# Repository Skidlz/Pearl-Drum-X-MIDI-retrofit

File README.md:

# Pearl Drum-X MIDI retrofit
 A MIDI retrofit board for Pearl's Drum-X (DRX-1) drum synthesizer

The project is designed around an Atmega*8 that controls a MAX528 octal DAC.

### Install Guide
[Here](https://docs.google.com/document/d/1SWIhVnxzadJWSYvPP88jSyq_Yxp76ufy1qYrGyIhOZM/edit?usp=sharing) is a quick explanation of the connections that need to be made to install the board.

### DAC
Five DAC outputs are used to generate triggers with different voltages based on MIDI velocity.

One output is used to generate eight control voltages for each of the five voices. Timing signals are received from the Pearl's motherboard, and are used to syncronize the stream of multiplexed CV signals.

### Use
The boards starts up in "MIDI learn" mode, and loads default settings for each voice. The board will assign itself to the first channel it receives a message on. The notes that it responds to, and the voice defaults are hard-coded in the firmware.

The voice paramaters are mapped to the first 40 MIDI CCs in this order: Pitch, Bend, Osc/Noise Mix, Over Tone, Attack, Filter, Decay, Level

### Atmega328p
The fuse bits of the Atmega328p need to be set for an external 16MHz crystal oscillator. The chips default to using the internal osc, and the firmware does not support this.
The following values can be programmed with avrdude: L:0xFF, H:0xD9, E:0xFF 

### Schematic

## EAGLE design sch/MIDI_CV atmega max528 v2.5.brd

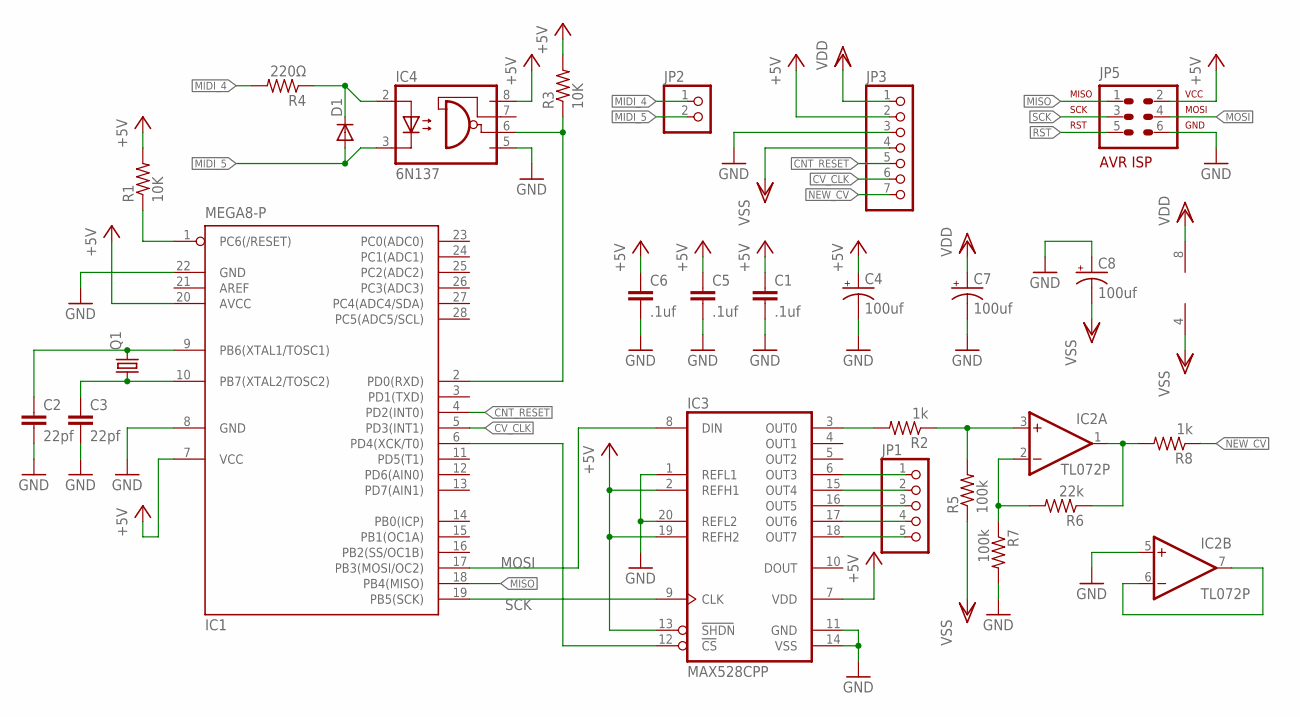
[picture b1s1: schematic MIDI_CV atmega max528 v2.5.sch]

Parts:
C1, C5, C6: .1uf; C025-024X044
C2, C3: 22pf; C025-024X044
C4, C7, C8: 100uf; E1,8-4
D1: DIODE-D-2.5; D-2.5
IC1: MEGA8-P; DIL28-3
IC2: TL072P; DIL08
IC3: MAX528CPP; DIL20
IC4: 6N137; DIL08
JP1: PINHD-1X5; 1X05
JP2: PINHD-1X2; 1X02
JP3: PINHD-1X7; 1X07
JP5: AVR-ISP-6VERT; AVR-ISP-6
Q1: CRYSTALHC18U-V; HC18U-V
R1, R3: 10K; 0204V
R2, R8: 1k; 0204V
R4: 220Ω; 0204V
R5, R7: 100k; 0204V
R6: 22k; 0204V

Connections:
+5V: C1.1, C4.+, C5.1, C6.1, IC1.7 (VCC), IC1.20 (AVCC), IC3.2 (REFH1), IC3.7 (VDD), IC3.13 (SHDN), IC3.19 (REFH2), IC4.8 (VCC), JP3.2, JP5.2, R1.2, R3.2
CNT_RESET: IC1.4 (PD2(INT0)), JP3.5
CV_CLK: IC1.5 (PD3(INT1)), JP3.6
GND: C1.2, C2.2, C3.2, C4.-, C5.2, C6.2, C7.-, C8.+, IC1.8 (GND), IC1.22 (GND), IC2.5 (+IN), IC3.1 (REFL1), IC3.11 (GND), IC3.14 (VSS), IC3.20 (REFL2), IC4.5 (GND), JP3.3, JP5.6, R7.2
MIDI_4: JP2.1, R4.2
MIDI_5: D1.A, IC4.3 (C), JP2.2
MISO: IC1.18 (PB4(MISO)), JP5.1
MOSI: IC1.17 (PB3(MOSI/OC2)), IC3.8 (DIN), JP5.4
unnamed: IC2.2 (-IN), R6.2, R7.1
unnamed: IC3.6 (OUT3), JP1.1
unnamed: IC3.15 (OUT4), JP1.2
unnamed: IC1.6 (PD4(XCK/T0)), IC3.12 (CS)
unnamed: IC3.16 (OUT5), JP1.3
unnamed: IC3.17 (OUT6), JP1.4
unnamed: D1.C, IC4.2 (A), R4.1
unnamed: IC3.18 (OUT7), JP1.5
unnamed: C2.1, IC1.9 (PB6(XTAL1/TOSC1)), Q1.2
unnamed: IC1.2 (PD0(RXD)), IC4.6 (VO), R3.1
unnamed: C3.1, IC1.10 (PB7(XTAL2/TOSC2)), Q1.1
unnamed: IC2.1 (OUT), R6.1, R8.2
unnamed: IC2.3 (+IN), R2.1, R5.2
unnamed: IC3.3 (OUT0), R2.2
unnamed: IC2.6 (-IN), IC2.7 (OUT)
NEW_CV: JP3.7, R8.1
RST: IC1.1 (PC6(/RESET)), JP5.5, R1.1
SCK: IC1.19 (PB5(SCK)), IC3.9 (CLK), JP5.3
VDD: C7.+, IC2.8 (V+), JP3.1
VSS: C8.-, IC2.4 (V-), JP3.4, R5.1

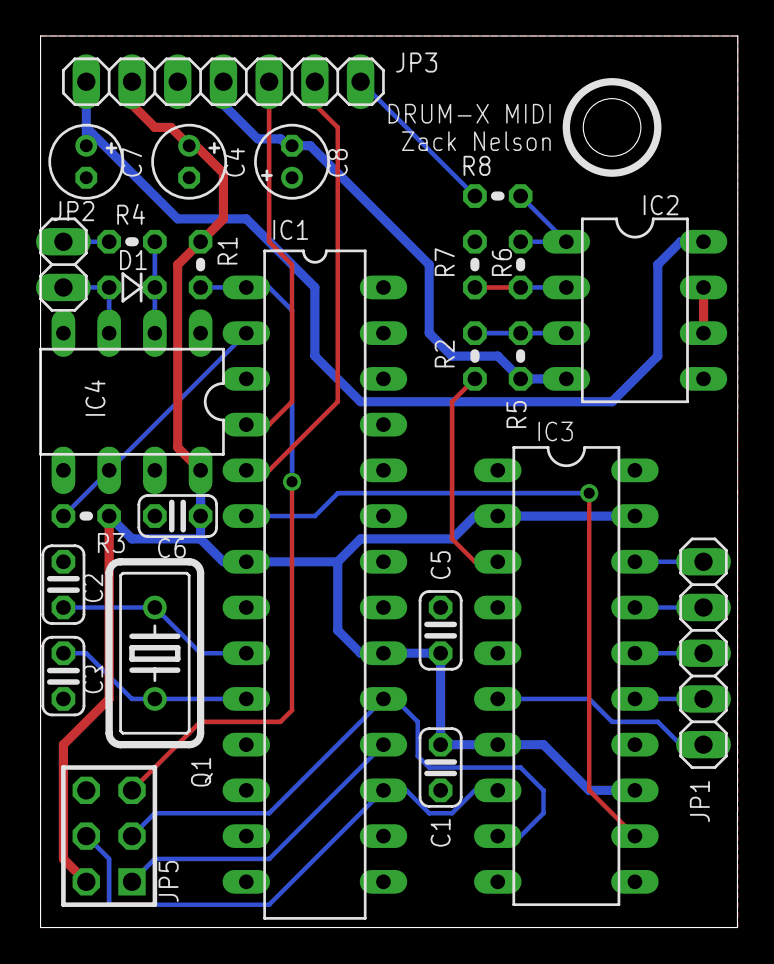
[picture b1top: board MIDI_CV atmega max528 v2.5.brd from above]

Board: 2 copper layers, 38.7 x 49.5 mm, 26 parts (0 on the bottom side), 28 nets.

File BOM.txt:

Qty Value         Device          Package      Parts      Description                          MF MPN       OC_FARNELL OC_NEWARK
1                 PINHD-1X2       1X02         JP2        PIN HEADER                                                            
1                 PINHD-1X5       1X05         JP1        PIN HEADER                                                            
1                 PINHD-1X7       1X07         JP3        PIN HEADER                                                            
3   .1uf          C-EU025-024X044 C025-024X044 C1, C5, C6 CAPACITOR, European symbol                                            
2   100k          R-US_0204/2V    0204V        R5, R7     RESISTOR, American symbol                                             
3   100uf         CPOL-USE1.8-4   E1,8-4       C4, C7, C8 POLARIZED CAPACITOR, American symbol                                  
2   10K           R-US_0204/2V    0204V        R1, R3     RESISTOR, American symbol                                             
1   16MHz         CRYSTALHC18U-V  HC18U-V      Q1         CRYSTAL                                           unknown    unknown  
1   1N4148        DIODE-D-2.5     D-2.5        D1         DIODE                                                                 
2   1k            R-US_0204/2V    0204V        R2, R8     RESISTOR, American symbol                                             
1   220Ω          R-US_0204/2V    0204V        R4         RESISTOR, American symbol                                             
1   22k           R-US_0204/2V    0204V        R6         RESISTOR, American symbol                                             
2   22pf          C-EU025-024X044 C025-024X044 C2, C3     CAPACITOR, European symbol                                            
1   6N137         6N137           DIL08        IC4        MOTOROLA OPTO COUPLER                   6N137     1328376    52M1895  
1   AVR-ISP-6VERT AVR-ISP-6VERT   AVR-ISP-6    JP5        AVR ISP-6 Serial Programming Header                                   
1   MAX528CPP     MAX528CPP       DIL20        IC3        DIGITAL/ANALOG CONVERTER                MAX528CPP 1379992    78C2818  
1   MEGA8-P       MEGA8-P         DIL28-3      IC1        MICROCONTROLLER                                   unknown    unknown  
1   TL072P        TL072P          DIL08        IC2        OP AMP

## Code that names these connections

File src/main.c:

// Pearl CV - Zack Nelson
#include <stdint.h>
#include <avr/io.h>
#include <avr/interrupt.h>
#include <util/delay.h>
#include "uart.h"
#include "midi.h"
#include "MAX528.h"

#define F_CPU 16000000UL

//Values per voice
//Pitch, Bend, Osc/Noise Mix, Over Tone, Attack, Filter, Decay, Level
uint8_t cvs[5][8] = {
        { 128, 96,  128, 128, 128, 128, 64,  128 },
        { 128, 128, 128, 64,  64,  128, 64,  128 },
        { 196, 128, 255, 128, 64,  128, 128, 128 },
        { 128, 128, 255, 128, 64,  128, 128, 128 },
        { 64,  128, 255, 128, 64,  128, 128, 128 }};

#define trig_max 57 //number of 5.7KHz cycles before trig turns off
uint8_t trig_cnt[5] = { 0, 0, 0, 0, 0 }; //time trigger has been high
uint8_t trig_velo[5] = { 127, 127, 127, 127, 127 }; //amplitude of trigger

uint8_t mux_cnt = 0;

ISR (INT0_vect) {
    mux_cnt = 0;
}

ISR (INT1_vect) { //write CV
    uint8_t x = mux_cnt & 0b111;
    uint8_t y = (mux_cnt >> 3) & 0b111;
    if (mux_cnt++ >= 40) mux_cnt = 0; //error catch
    uint8_t cv = cvs[y][x]; //lookup CV
    max_wr_command(0b1, cv); //write CV to out0

    for (int voice = 0; voice < 5; voice++) {
        if (trig_cnt[voice]) { //if trig active
            if (trig_cnt[voice] == 1) { //turn trig on
                max_wr_command(0b1000 << voice, trig_velo[voice]); //write CV
            } else if (trig_cnt[voice] >= trig_max) { //trig turn off
                max_wr_command(0b1000 << voice, 0); //write CV
            }

            trig_cnt[voice]++;
        }
    }
}

void note_on(uint8_t note, uint8_t vel) {
    uint8_t voice = 0xff;
    switch (note) {
        case 48://35: //Bass
        case 49://36: //Kick
            voice = 0;
            break;
        case 50://38: //Snare
        case 51://40: //Electronic Snare
            voice = 1;
            break;
        case 52://43: //Floor tom
        case 53://45: //Low Tom
            voice = 2;
            break;
        case 54://47: //Low-Mid Tom
        case 55://48: //High-Mid Tom
            voice = 3;
            break;
        case 56://50: //High Tom
            voice = 4;
    }

    if (voice != 0xff) {
        trig_cnt[voice] = 1; //enable
        trig_velo[voice] = vel << 1; //set velocity
    }
}

void control_change(uint8_t param, uint8_t val) {
    //calculate position in voice value matrix
    uint8_t x = param & 0b111;
    uint8_t y = param >> 3;

    if (y >= 4) y = 4;
    cvs[y][x] = val << 1; //store value
}

int main() {
    uart_init(31250);

    set_cntrl_chng(control_change); //set function to handle control changes
    set_MIDI_key_press(note_on); //set function to handle note on
    //set_MIDI_key_release(); //set function to handle note off

    UCSR0B &= ~(1 << TXEN0); //Disable transmitter

    cli();// disable all interrupts

    //setup external interrupts
    EICRA |= (1 << ISC11) | (1 << ISC10) | (1 << ISC01) | (1 << ISC00); //rising edge
    //MCUCR |= (1 << ISC11) | (1 << ISC10) | (1 << ISC01) | (1 << ISC00); //rising edge
    EIMSK |= (1 << INT1) | (1 << INT0); //enable int
    //GIMSK |= (1 << INT1) | (1 << INT0);      // Turns on INT0

    DDRB = 0xff; //DAC SPI data bus
    //PB3 MOSI
    //PB4 MISO
    //PB5 SCK
    DDRC = 0b00111111; //switch outputs
    //PC1 CV Switch
    DDRD = 0b11110010; //0=input
    //PD0 = MIDI in
    //PD2 = INT0 = Count Reset
    //PD3 = INT1 = CV clock
    //PD4 = DAC CS
    PORTD = 0b1000; //pullup INT pin
    PORTB = 0;
    PORTC = 0; //switches off

    //-------------------------------
    max_init(); //configure DAC
    _delay_ms(1);

    sei();// enable all interrupts

    while (1) if (uart_test()) handle_midi();

    return 1;
}

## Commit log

2025-02-01 init
2025-04-19 Adding BOM
2025-04-19 Update README.md
    Added fuse bits
